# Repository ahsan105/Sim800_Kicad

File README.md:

# Sim800_Kicad
This project is a hobby project. The board hosts Sim800 IC that provides the GPRS capabilities to the board and added different serial protocols to provide ease of connection and also has sim card holder. Also the board has its own power supply that converts the output to 4.4V that goes to the IC.

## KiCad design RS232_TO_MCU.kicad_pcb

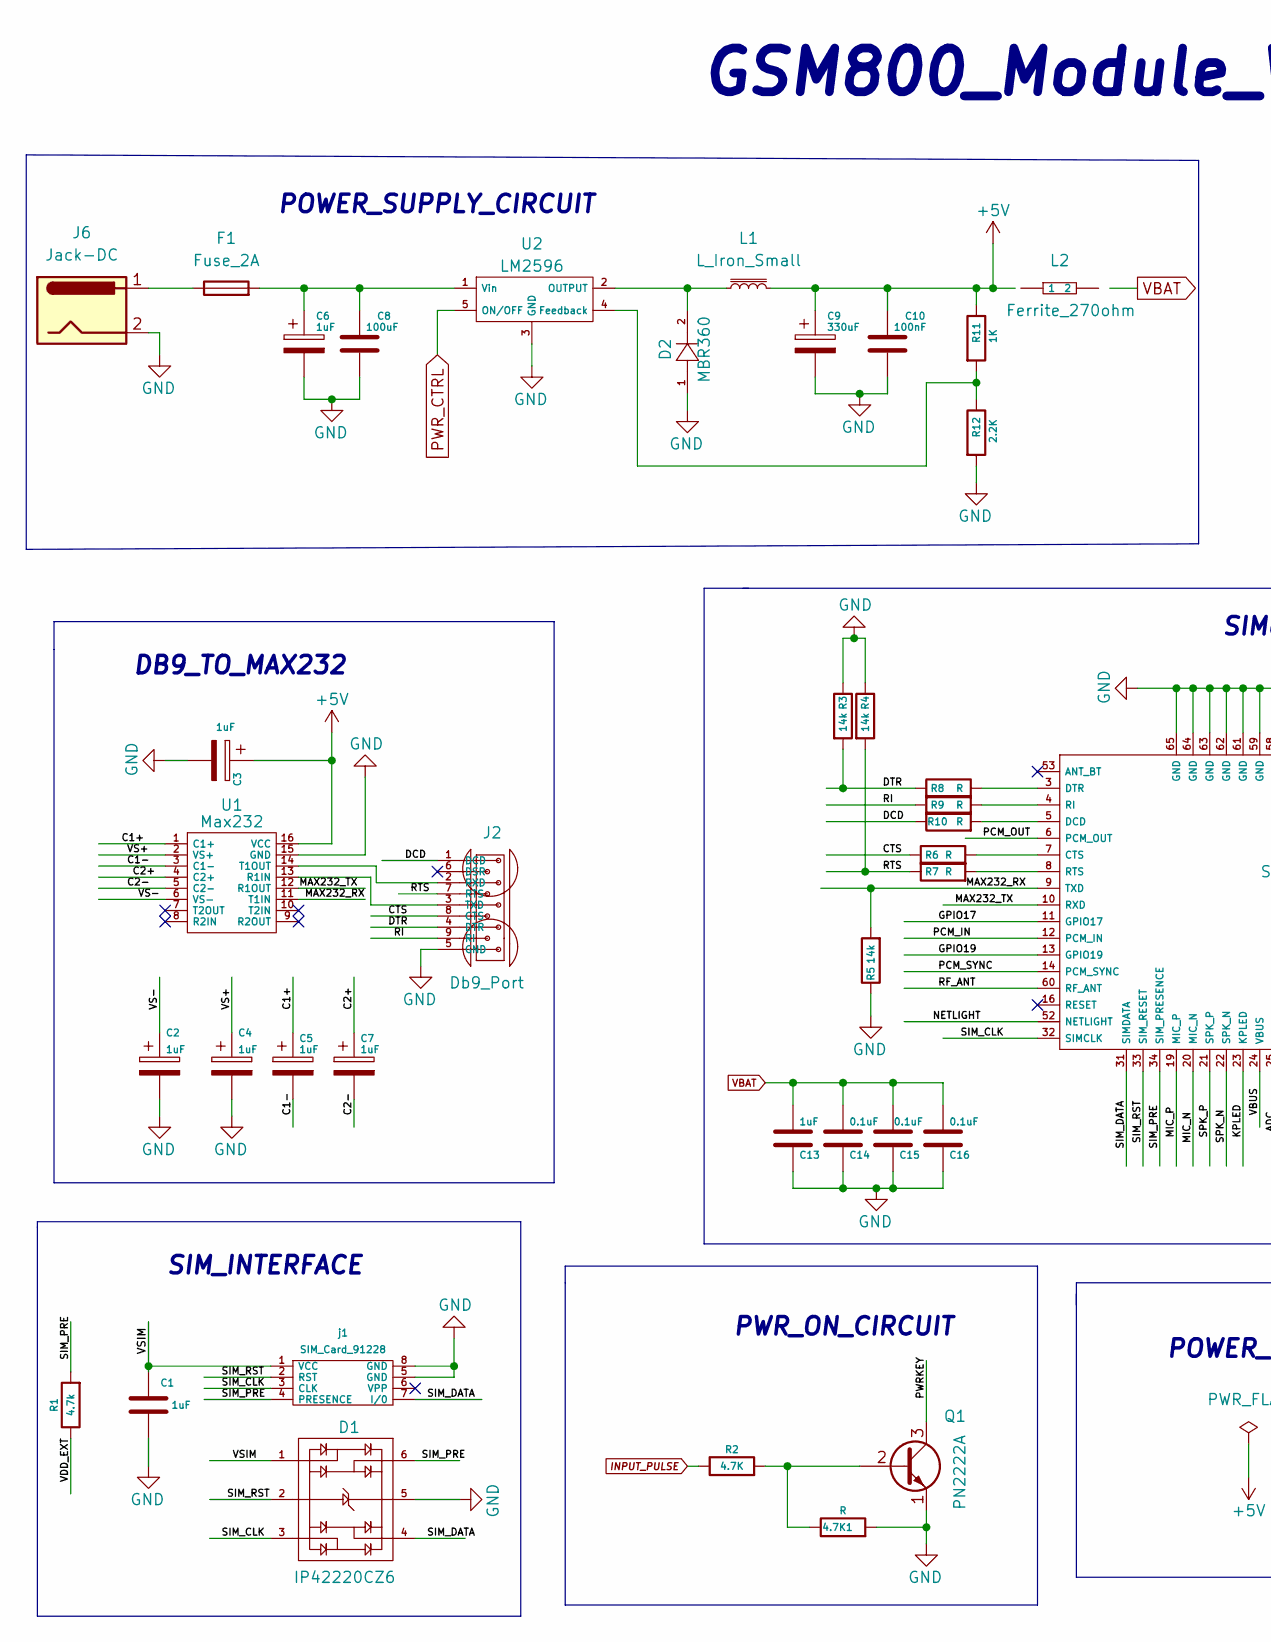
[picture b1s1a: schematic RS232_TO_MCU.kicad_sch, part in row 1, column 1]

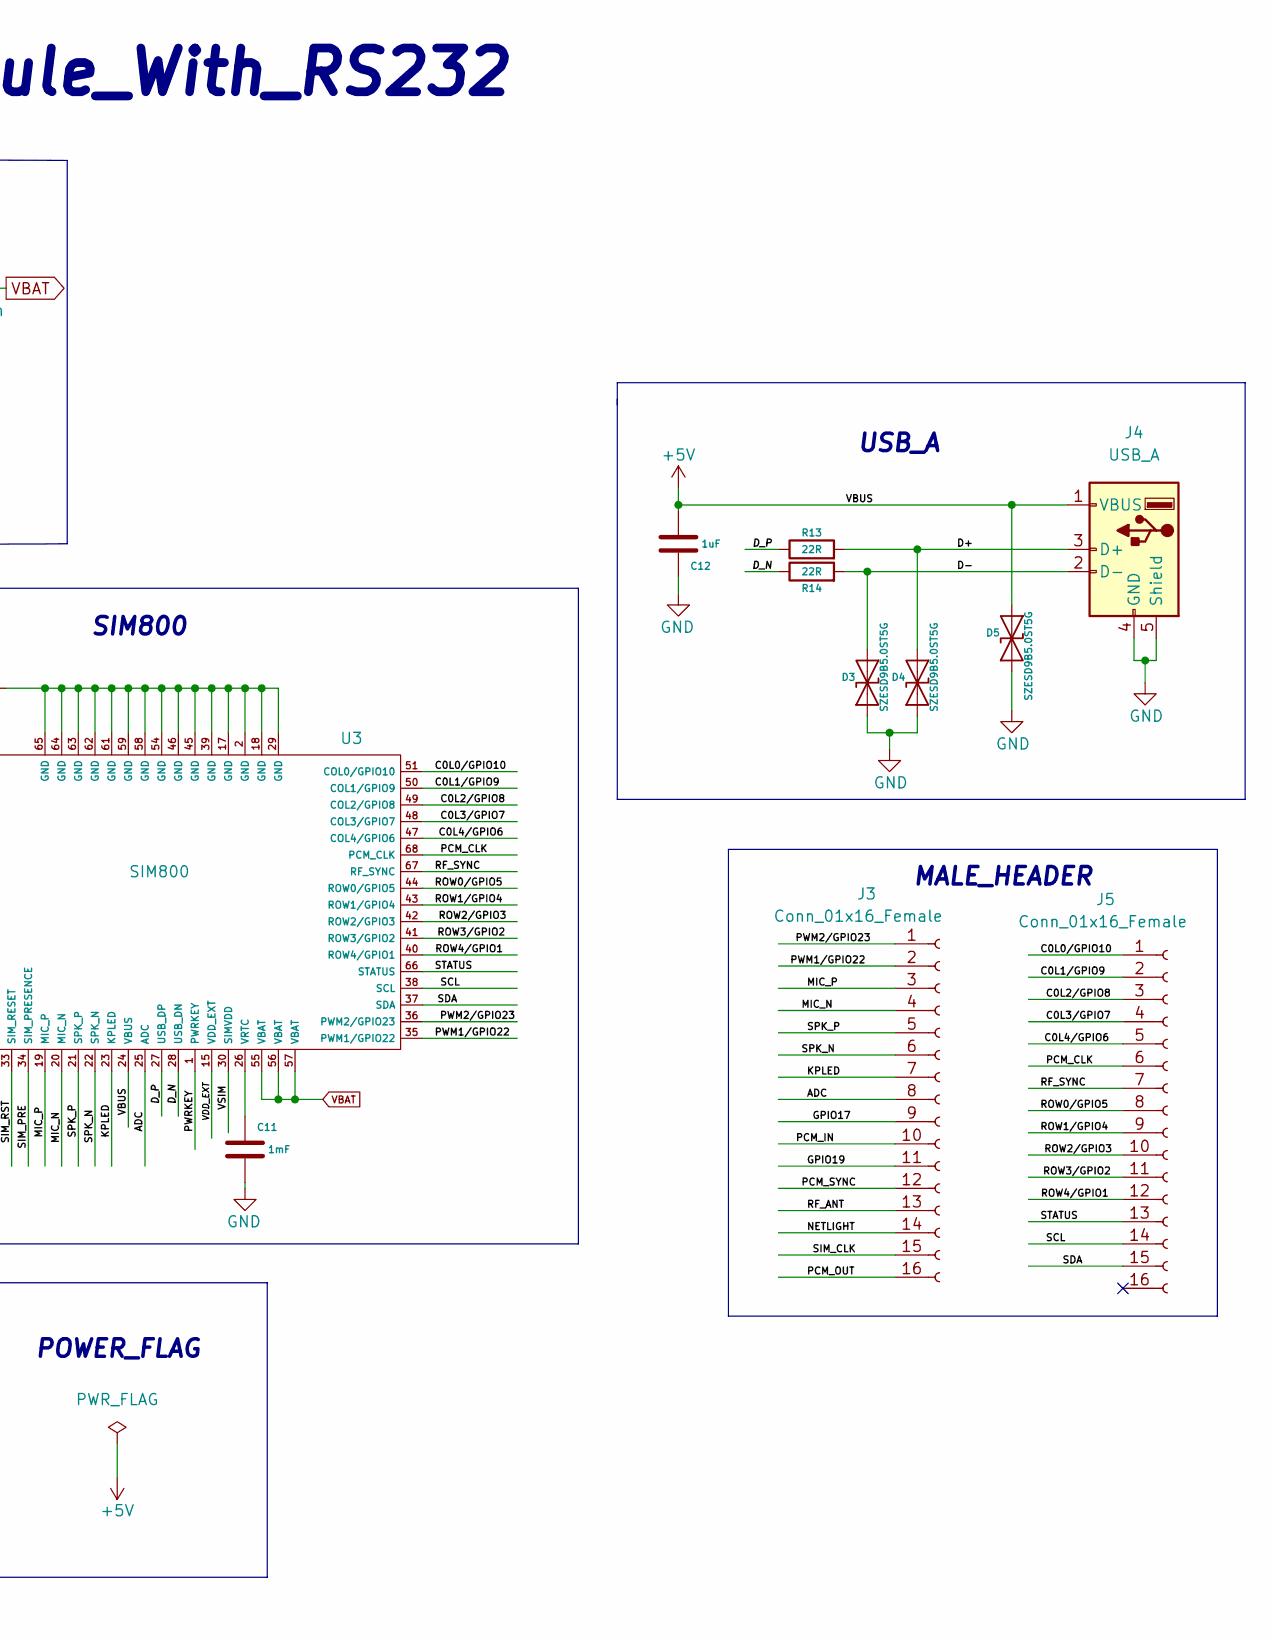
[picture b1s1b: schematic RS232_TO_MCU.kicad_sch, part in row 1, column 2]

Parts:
4.7K1: R; C_0603_1608Metric
C1, C2, C3, C4, C5, C6, C7, C12, C13: 1uF; C_0603_1608Metric
C8: 100uF; C_0603_1608Metric
C9: 330uF; C_0603_1608Metric
C10: 100nF; C_0603_1608Metric
C11: 1mF; C_0603_1608Metric
C14, C15, C16: 0.1uF; C_0603_1608Metric
D1: IP42220CZ6
D2: MBR360
D3, D4, D5: SZESD9B5.0ST5G; D_SOD-923
F1: Fuse_2A; Fuse_0603_1608Metric
J2: Db9_Port; Db9
J3, J5: Conn_01x16_Female; Header_1x16
J4: USB_A; USB_Mini-B_Lumberg_2486_01_Horizontal
J6: Jack-DC; BarrelJack_CUI_PJ-102AH_Horizontal
L1: L_Iron_Small; L_0805_2012Metric
L2: Ferrite_270ohm; Ferrite_bead
Q1: PN2222A; TO-92_Inline
R1: 4.7k; C_0603_1608Metric
R2: 4.7K; C_0603_1608Metric
R3, R4, R5: 14k; C_0603_1608Metric
R6, R7, R8, R9, R10: R; C_0603_1608Metric
R11: 1K; C_0603_1608Metric
R12: 2.2K; C_0603_1608Metric
R13, R14: 22R; C_0603_1608Metric
U1: Max232; max232
U2: LM2596
U3: SIM800
j1: SIM_Card_91228; SimCard_91228

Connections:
+5V: C3.1, C9.1, C10.1, C12.2, D5.2 (A2), J4.1 (VBUS), L1.2, R11.1, U1.16 (VCC), U3.24 (VBUS)
/ADC: J3.8, U3.25 (ADC)
/C0L0/GPIO10: J5.1, U3.51 (COL0/GPIO10)
/C0L1/GPIO9: J5.2, U3.50 (COL1/GPIO9)
/C0L2/GPIO8: J5.3, U3.49 (COL2/GPIO8)
/C0L3/GPIO7: J5.4, U3.48 (COL3/GPIO7)
/C0L4/GPIO6: J5.5, U3.47 (COL4/GPIO6)
/C1+: C5.1, U1.1 (C1+)
/C1-: C5.2, U1.3 (C1-)
/C2+: C7.1, U1.4 (C2+)
/C2-: C7.2, U1.5 (C2-)
/CTS: J2.8 (CTS), R6.1
/D+: D4.2 (A2), J4.3 (D+), R13.2
/D-: D3.2 (A2), J4.2 (D-), R14.2
/DCD: J2.1 (DCD), R10.1
/DTR: J2.4 (DTR), R3.2, R8.1
/D_N: R14.1, U3.28 (USB_DN)
/D_P: R13.1, U3.27 (USB_DP)
/GPIO17: J3.9, U3.11 (GPIO17)
/GPIO19: J3.11, U3.13 (GPIO19)
/KPLED: J3.7, U3.23 (KPLED)
/MAX232_RX: R5.2, U1.11 (T1IN), U3.9 (TXD)
/MAX232_TX: U1.12 (R1OUT), U3.10 (RXD)
/MIC_N: J3.4, U3.20 (MIC_N)
/MIC_P: J3.3, U3.19 (MIC_P)
/NETLIGHT: J3.14, U3.52 (NETLIGHT)
/PCM_CLK: J5.6, U3.68 (PCM_CLK)
/PCM_IN: J3.10, U3.12 (PCM_IN)
/PCM_OUT: J3.16, U3.6 (PCM_OUT)
/PCM_SYNC: J3.12, U3.14 (PCM_SYNC)
/PWM1/GPIO22: J3.2, U3.35 (PWM1/GPIO22)
/PWM2/GPIO23: J3.1, U3.36 (PWM2/GPIO23)
/PWRKEY: Q1.3 (C), U3.1 (PWRKEY)
/RF_ANT: J3.13, U3.60 (RF_ANT)
/RF_SYNC: J5.7, U3.67 (RF_SYNC)
/RI: J2.9 (RI), R9.1
/ROW0/GPIO5: J5.8, U3.44 (ROW0/GPIO5)
/ROW1/GPIO4: J5.9, U3.43 (ROW1/GPIO4)
/ROW2/GPIO3: J5.10, U3.42 (ROW2/GPIO3)
/ROW3/GPIO2: J5.11, U3.41 (ROW3/GPIO2)
/ROW4/GPIO1: J5.12, U3.40 (ROW4/GPIO1)
/RTS: J2.7 (RTS), R4.2, R7.1
/SCL: J5.14, U3.38 (SCL)
/SDA: J5.15, U3.37 (SDA)
/SIM_CLK: D1.3, J3.15, U3.32 (SIMCLK), j1.3 (CLK)
/SIM_DATA: D1.4, U3.31 (SIMDATA), j1.7 (I/0)
/SIM_PRE: D1.6, R1.2, U3.34 (SIM_PRESENCE), j1.4 (PRESENCE)
/SIM_RST: D1.2, U3.33 (SIM_RESET), j1.2 (RST)
/SPK_N: J3.6, U3.22 (SPK_N)
/SPK_P: J3.5, U3.21 (SPK_P)
/STATUS: J5.13, U3.66 (STATUS)
/VDD_EXT: R1.1, U3.15 (VDD_EXT)
/VS+: C4.1, U1.2 (VS+)
/VS-: C2.1, U1.6 (VS-)
/VSIM: C1.1, D1.1, U3.30 (SIMVDD), j1.1 (VCC)
GND: 4.7K1.2, C1.2, C2.2, C3.2, C4.2, C6.2, C8.2, C9.2, C10.2, C11.2, C12.1, C13.1, C14.1, C15.1, C16.1, D1.5, D2.1, D3.1 (A1), D4.1 (A1), D5.1 (A1), J2.5 (GND), J4.4 (GND), J4.5 (Shield), J6.2, Q1.1 (E), R3.1, R4.1, R5.1, R12.2, U1.15 (GND), U2.3 (GND), U3.2 (GND), U3.17 (GND), U3.18 (GND), U3.29 (GND), U3.39 (GND), U3.45 (GND), U3.46 (GND), U3.54 (GND), U3.58 (GND), U3.59 (GND), U3.61 (GND), U3.62 (GND), U3.63 (GND), U3.64 (GND), U3.65 (GND), j1.5 (GND), j1.8 (GND)
INPUT_PULSE: R2.1
unnamed: 4.7K1.1, Q1.2 (B), R2.2
unnamed: C6.1, C8.1, F1.2, U2.1 (Vin)
unnamed: C11.1, U3.26 (VRTC)
unnamed: D2.2, L1.1, U2.2 (OUTPUT)
unnamed: F1.1, J6.1
unnamed: J2.2 (RXD), U1.14 (T1OUT)
unnamed: J2.3 (TXD), U1.13 (R1IN)
unnamed: R6.2, U3.7 (CTS)
unnamed: R7.2, U3.8 (RTS)
unnamed: R8.2, U3.3 (DTR)
unnamed: R9.2, U3.4 (RI)
unnamed: R10.2, U3.5 (DCD)
unnamed: L2.1, R11.2, R12.1, U2.4 (Feedback)
PWR_CTRL: U2.5 (ON/OFF)
VBAT: C13.2, C14.2, C15.2, C16.2, L2.2, U3.55 (VBAT), U3.56 (VBAT), U3.57 (VBAT)

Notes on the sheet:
MALE_HEADER
PWR_ON_CIRCUIT
SIM800
POWER_FLAG
SIM_INTERFACE
POWER_SUPPLY_CIRCUIT
GSM800_Module_With_RS232
DB9_TO_MAX232
USB_A

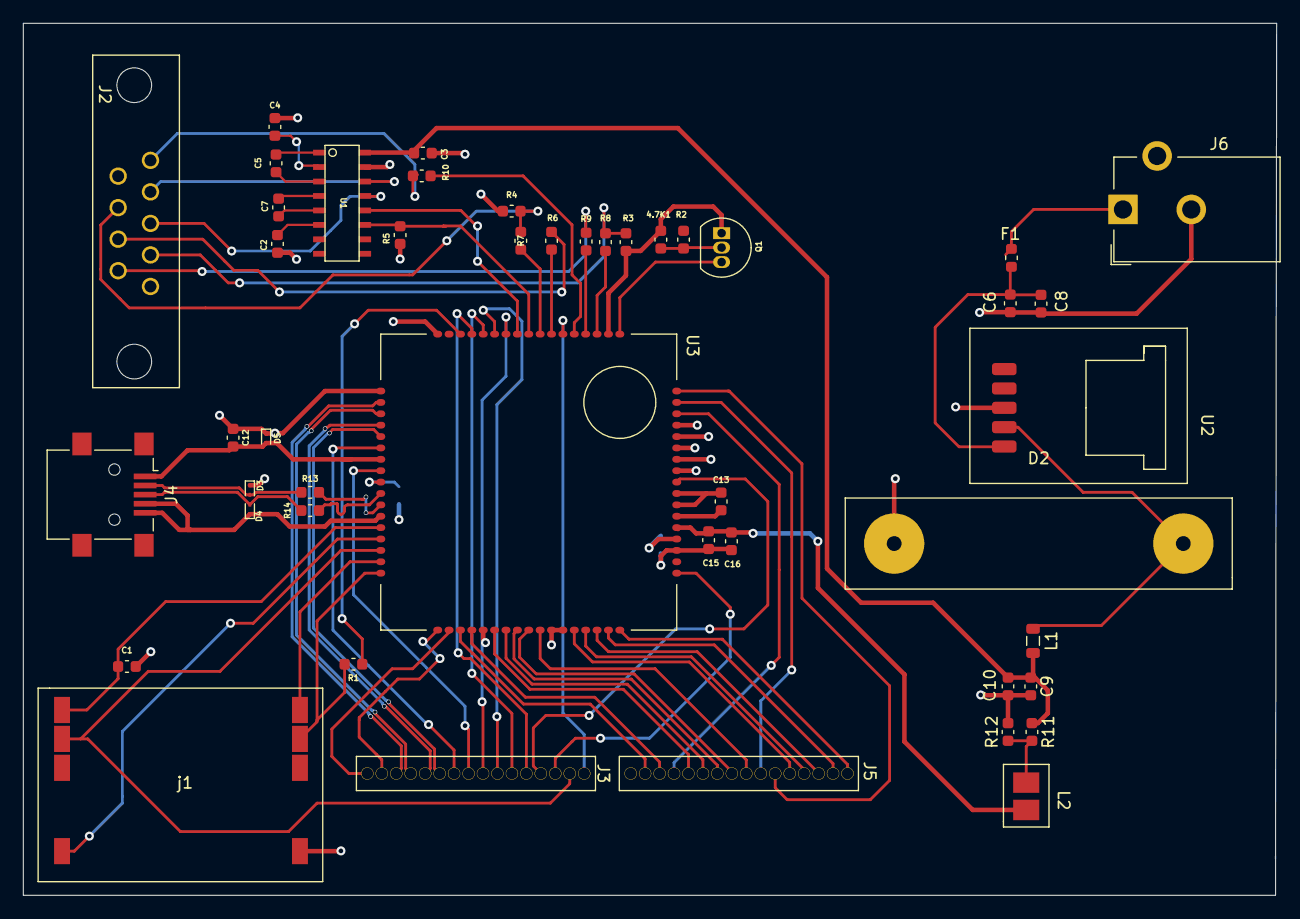
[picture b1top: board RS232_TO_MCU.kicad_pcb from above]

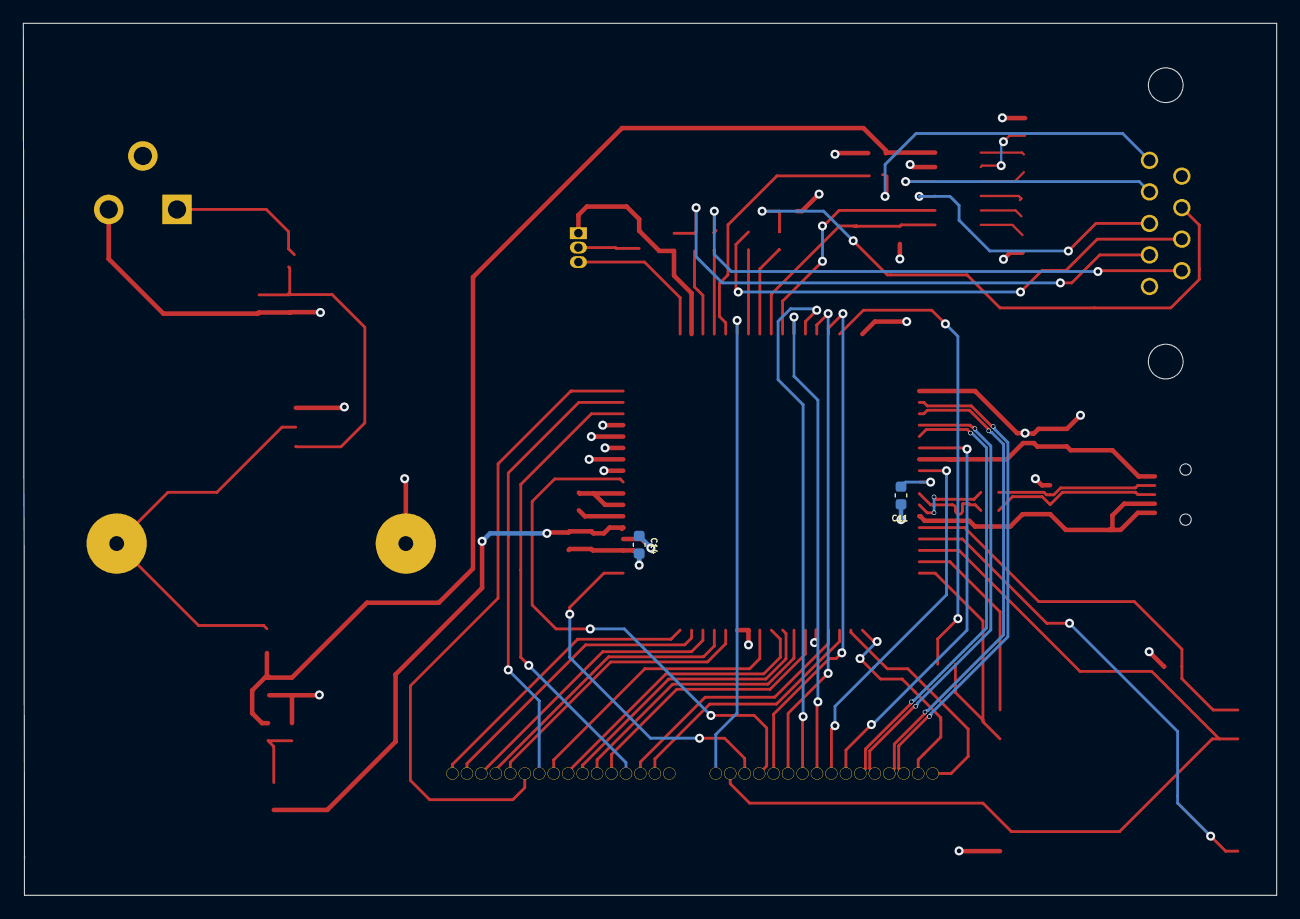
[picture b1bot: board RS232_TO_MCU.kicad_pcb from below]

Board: 4 copper layers, 110.1 x 76.6 mm, 48 parts (2 on the bottom side), 70 nets.
